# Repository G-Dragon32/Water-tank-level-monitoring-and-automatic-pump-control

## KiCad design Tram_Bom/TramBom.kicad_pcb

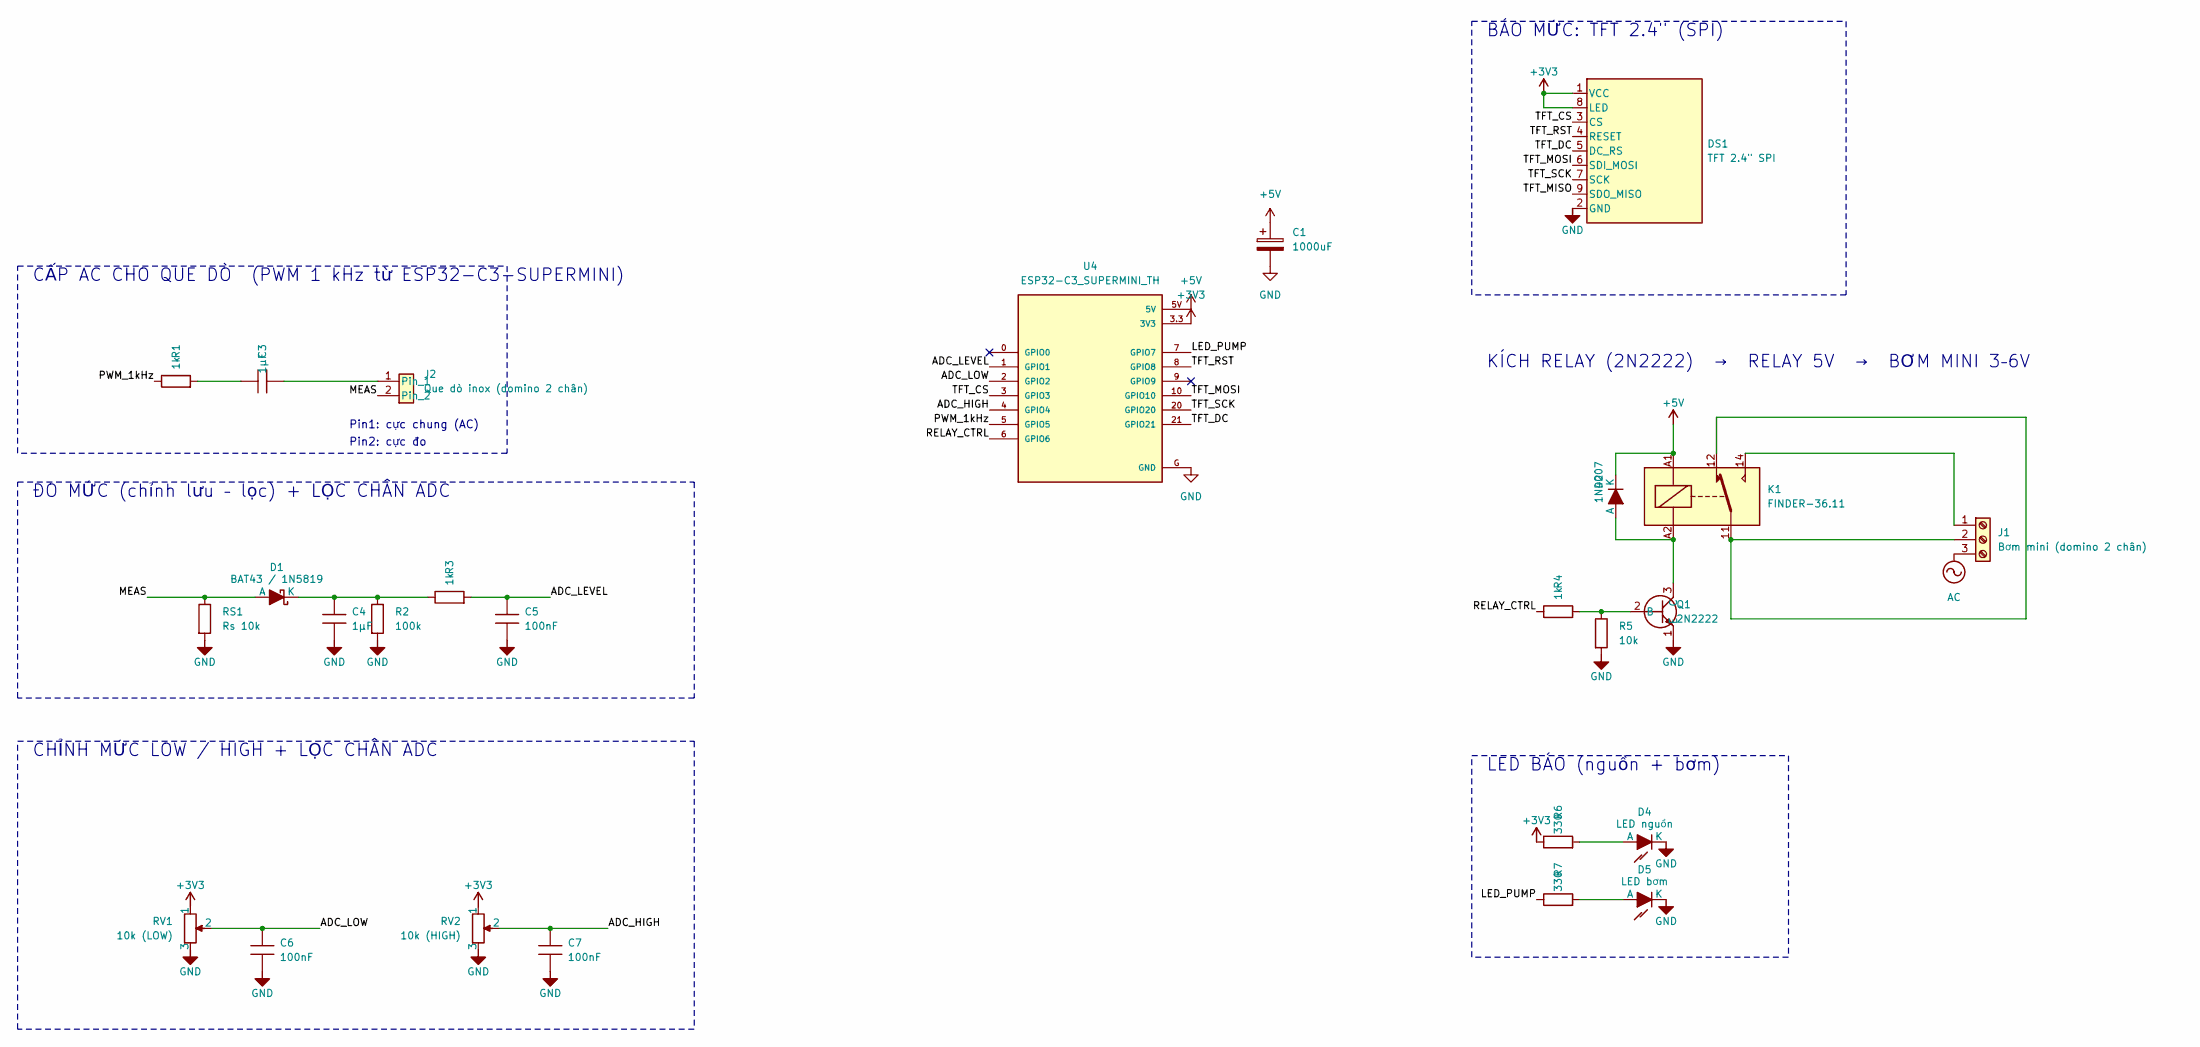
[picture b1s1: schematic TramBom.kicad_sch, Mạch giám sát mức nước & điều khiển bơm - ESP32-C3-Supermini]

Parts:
C1: 1000uF; CP_Radial_D8.0mm_P3.50mm
C3, C4: 1µF; C_Rect_L26.5mm_W11.5mm_P22.50mm_MKS4
C5, C6, C7: 100nF; C_Disc_D5.0mm_W2.5mm_P2.50mm
D1: BAT43 / 1N5819; D_DO-41_SOD81_P10.16mm_Horizontal
D2: 1N4007; D_DO-41_SOD81_P10.16mm_Horizontal
D4: LED nguồn; LED_D5.0mm
D5: LED bơm; LED_D5.0mm
DS1: TFT 2.4" SPI; PinSocket_1x09_P2.54mm_Vertical
J1: Bơm mini (domino 2 chân); TerminalBlock_Phoenix_MKDS-1,5-3_1x03_P5.00mm_Horizontal
J2: Que dò inox (domino 2 chân); PhoenixContact_MSTBA_2,5_2-G-5,08_1x02_P5.08mm_Horizontal
K1: FINDER-36.11; Relay_SPDT_Finder_36.11
Q1: 2N2222; TO-92L_Inline
R1, R3, R4: 1k; R_Axial_DIN0207_L6.3mm_D2.5mm_P10.16mm_Horizontal
R2: 100k; R_Axial_DIN0207_L6.3mm_D2.5mm_P10.16mm_Horizontal
R5: 10k; R_Axial_DIN0207_L6.3mm_D2.5mm_P10.16mm_Horizontal
R6, R7: 330; R_Axial_DIN0207_L6.3mm_D2.5mm_P10.16mm_Horizontal
RS1: Rs 10k; R_Axial_DIN0207_L6.3mm_D2.5mm_P10.16mm_Horizontal
RV1: 10k (LOW); Potentiometer_Runtron_RM-063_Horizontal
RV2: 10k (HIGH); Potentiometer_Runtron_RM-063_Horizontal
U4: ESP32-C3_SUPERMINI_TH; ESP32-C3_SuperMini_15.24mm; MPN ESP32-C3 SuperMini_TH

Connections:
+3V3: DS1.1 (VCC), DS1.8 (LED), R6.1, RV1.1, RV2.1, U4.3.3 (3V3); also elsewhere on the board
+5V: C1.1, D2.1 (K), K1.A1, U4.5V; also elsewhere on the board
/ADC_HIGH: C7.1, RV2.2, U4.4 (GPIO4); also elsewhere on the board
/ADC_LEVEL: C5.1, R3.2, U4.1 (GPIO1); also elsewhere on the board
/ADC_LOW: C6.1, RV1.2, U4.2 (GPIO2); also elsewhere on the board
/LED_PUMP: R7.1, U4.7 (GPIO7); also elsewhere on the board
/MEAS: D1.2 (A), J2.2, RS1.1
/PWM_1kHz: R1.1, U4.5 (GPIO5); also elsewhere on the board
/RELAY_CTRL: R4.1, U4.6 (GPIO6); also elsewhere on the board
/TFT_CS: DS1.3 (CS), U4.3 (GPIO3); also elsewhere on the board
/TFT_DC: DS1.5 (DC_RS), U4.21 (GPIO21); also elsewhere on the board
/TFT_MISO: DS1.9 (SDO_MISO)
/TFT_MOSI: DS1.6 (SDI_MOSI), U4.10 (GPIO10); also elsewhere on the board
/TFT_RST: DS1.4 (RESET), U4.8 (GPIO8); also elsewhere on the board
/TFT_SCK: DS1.7 (SCK), U4.20 (GPIO20); also elsewhere on the board
GND: C1.2, C4.2, C5.2, C6.2, C7.2, D4.1 (K), D5.1 (K), DS1.2 (GND), Q1.1 (E), R2.2, R5.2, RS1.2, RV1.3, RV2.3, U4.G (GND); also elsewhere on the board
unnamed: C3.1, R1.2
unnamed: C4.1, D1.1 (K), R2.1, R3.1
unnamed: D2.2 (A), K1.A2, Q1.3 (C)
unnamed: D4.2 (A), R6.2
unnamed: D5.2 (A), R7.2
unnamed: J1.1, K1.14
unnamed: J1.2, K1.11, K1.12
unnamed: C3.2, J2.1
unnamed: Q1.2 (B), R4.2, R5.1

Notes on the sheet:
CHỈNH MỨC LOW / HIGH + LỌC CHÂN ADC
ĐO MỨC (chỉnh lưu – lọc) + LỌC CHÂN ADC
Pin1: cực chung (AC)
LED BÁO (nguồn + bơm)
Pin2: cực đo
CẤP AC CHO QUE DÒ (PWM 1 kHz từ ESP32-C3-SUPERMINI)
BÁO MỨC: TFT 2.4" (SPI)
KÍCH RELAY (2N2222) → RELAY 5V → BƠM MINI 3–6V

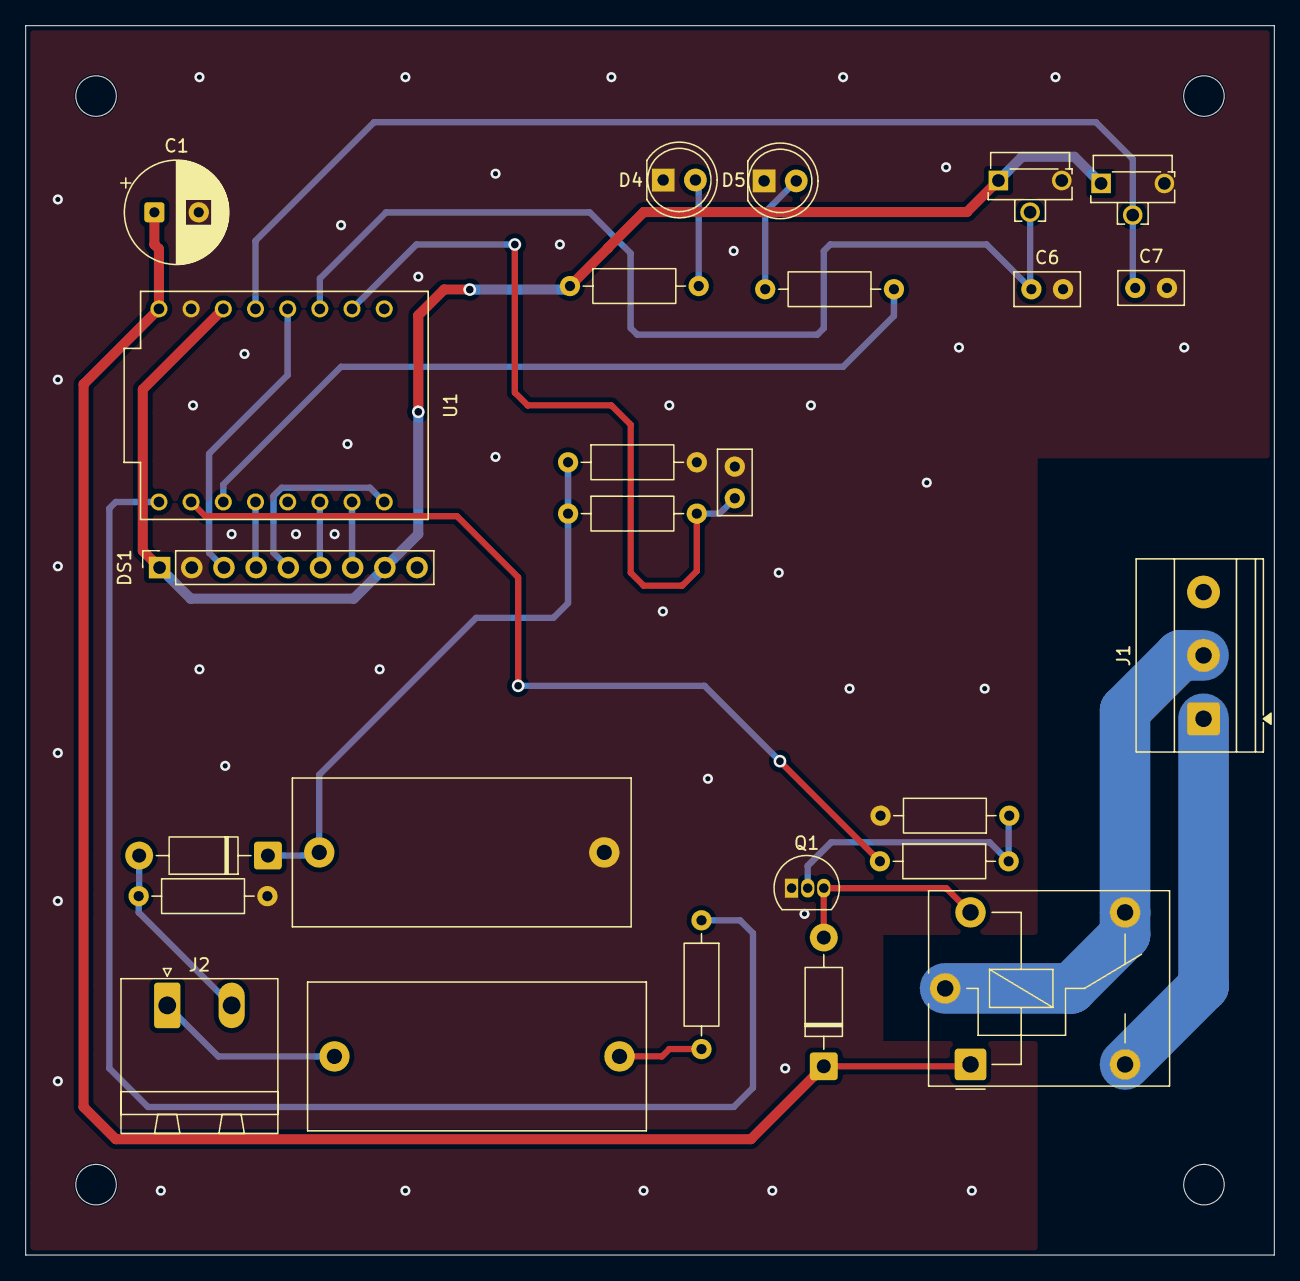
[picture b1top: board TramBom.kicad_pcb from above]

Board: 2 copper layers, 98.6 x 97.0 mm, 26 parts (0 on the bottom side), 24 nets.

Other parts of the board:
U1: ESP32-C3_SUPERMINI_TH; MODULE_ESP32-C3_SUPERMINI_TH

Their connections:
+3V3: U1.3.3 (3V3); also elsewhere on the board
+5V: U1.5V; also elsewhere on the board
/ADC_HIGH: U1.4 (GPIO4); also elsewhere on the board
/ADC_LEVEL: U1.1 (GPIO1); also elsewhere on the board
/ADC_LOW: U1.2 (GPIO2); also elsewhere on the board
/LED_PUMP: U1.7 (GPIO7); also elsewhere on the board
/PWM_1kHz: U1.5 (GPIO5); also elsewhere on the board
/RELAY_CTRL: U1.6 (GPIO6); also elsewhere on the board
/TFT_CS: U1.3 (GPIO3); also elsewhere on the board
/TFT_DC: U1.21 (GPIO21); also elsewhere on the board
/TFT_MOSI: U1.10 (GPIO10); also elsewhere on the board
/TFT_RST: U1.8 (GPIO8); also elsewhere on the board
/TFT_SCK: U1.20 (GPIO20); also elsewhere on the board
GND: U1.G (GND); also elsewhere on the board
